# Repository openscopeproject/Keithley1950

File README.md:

# Keithley 195A DMM Option 1950

Keithley Instruments 195A Digital Multimeter is a 5½ digit resolution 200 000
count instrument that was manufactured in the 80's, possibly early 90's. It was
available in two configurations: base model that only had DC Volts and Ohms
measurements and model with 1950 option, which added DC/AC Amps and AC TRMS
Volts measurements.

Keithley DMM line has long replaced 195/196/199 series with newer models but
these still show up on Ebay and other outlets and they offer great performance
for reasonable prices. Unfortunately most of the 195A models available online
are the ones without 1950 Option.

This project aims to recreate the 1950 Option PCB and circuitry using modern
components.

In the process some upgrades and some compromises were made. For example this
version of 1950 option board is based on AD8436 trms chip that along with newer
opamps provides higher bandwidth and better overall specs than much older AD536
of the original. On the other hand cheaper shunt resistors are used (because
of their availability) with worse drift and tempco characteristics.

**High voltage** operation using the new board is also **NOT** recommended or
tested.

---

## BOM

See [bom](https://openscopeproject.org/InteractiveHtmlBomDemo/html/Keithley1950.html)
for this board generated by
[InteractiveHtmlBom](https://github.com/openscopeproject/InteractiveHtmlBom)
plugin for KiCad.

## Schematic

## 3D render

## Pictures

End result installed in the meter

Original board next to new version

Close up of rev A board with Genuine Bodge™ visible on the left

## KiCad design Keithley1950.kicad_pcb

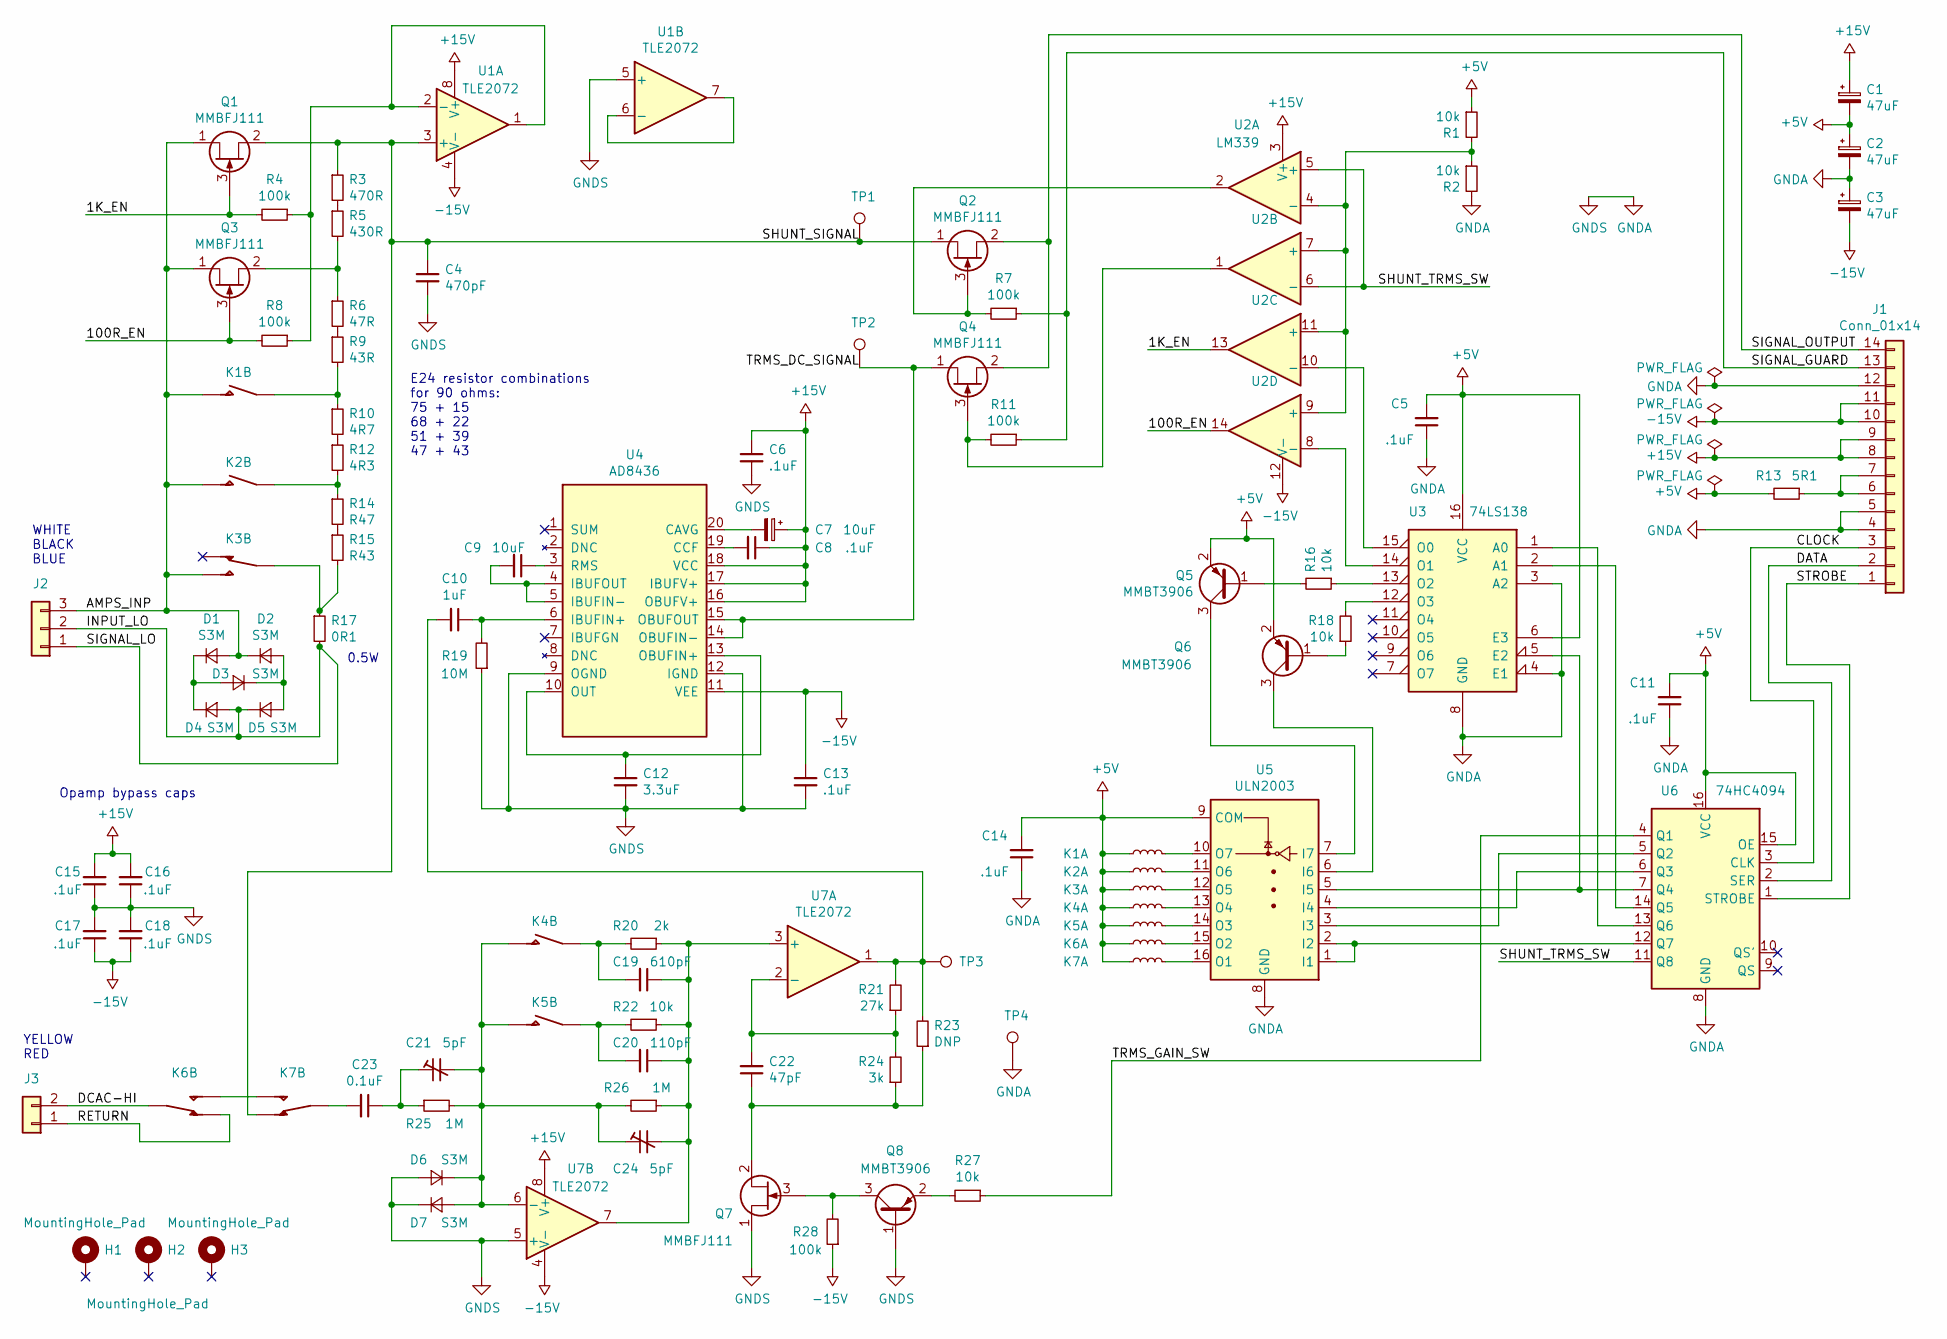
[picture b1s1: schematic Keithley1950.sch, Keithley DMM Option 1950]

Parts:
C1, C2, C3: 47uF; CP_Elec_6.3x5.9
C4: 470pF; C_0805_2012Metric
C5, C6, C8, C11, C13, C14, C15, C16, C17, C18: .1uF; C_0603_1608Metric
C7: 10uF; CP_EIA-3528-21_Kemet-B
C9: 10uF; C_0805_2012Metric
C10: 1uF; C_0805_2012Metric
C12: 3.3uF; C_0805_2012Metric
C19: 610pF; C_0805_2012Metric
C20: 110pF; C_0805_2012Metric
C21, C24: 5pF; MURATA_TZ03
C22: 47pF; C_0805_2012Metric
C23: 0.1uF; C_Rect_L18.0mm_W5.0mm_P15.00mm_FKS3_FKP3
D1, D2, D3, D4, D5, D6, D7: S3M; D_SMB
H1, H2, H3: MountingHole_Pad; MountingHole_3.2mm_M3_Pad_Via
J1: Conn_01x14; DIP-14_W7.62mm_Socket_LongPads
J2: Conn_01x03; TerminalBlock_Phoenix_PT-1,5-3-5.0-H_1x03_P5.00mm_Horizontal
J3: Conn_01x02; TerminalBlock_Phoenix_PT-1,5-2-5.0-H_1x02_P5.00mm_Horizontal
K1, K2, K4, K5: Relay_SP2P; Relay_SPST_StandexMeder_SIL_Form1A
K3, K6, K7: Relay_SP3P; Relay_SPDT_SANYOU_SRD_Series_Form_C
Q1, Q2, Q3, Q4, Q7: MMBFJ111; SOT-23
Q5, Q6, Q8: MMBT3906; SOT-23
R1, R2, R16, R18, R22, R27: 10k; R_0805_2012Metric
R3: 470R; R_0805_2012Metric
R4, R7, R8, R11, R28: 100k; R_0805_2012Metric
R5: 430R; R_0805_2012Metric
R6: 47R; R_0805_2012Metric
R9: 43R; R_0805_2012Metric
R10: 4R7; R_0805_2012Metric
R12: 4R3; R_0805_2012Metric
R13: 5R1; R_2512_6332Metric
R14: R47; R_2512_6332Metric
R15: R43; R_2512_6332Metric
R17: 0R1; R_2512_With_10mm_axial
R19: 10M; R_0805_2012Metric
R20: 2k; R_0805_2012Metric
R21: 27k; R_0805_2012Metric
R23: DNP; R_0805_2012Metric
R24: 3k; R_0805_2012Metric
R25, R26: 1M; R_0805_2012Metric
TP1, TP2, TP3: TestPoint; TestPoint_Pad_D2.5mm
TP4: TestPoint; TestPoint_THTPad_D1.5mm_Drill0.7mm
U1, U7: TLE2072; SOIC-8_3.9x4.9mm_P1.27mm
U2: LM339; SOIC-14_3.9x8.7mm_P1.27mm
U3: 74LS138; SOIC-16_3.9x9.9mm_P1.27mm
U4: AD8436; QSOP-20_3.9x8.7mm_P0.635mm
U5: ULN2003; SOIC-16_3.9x9.9mm_P1.27mm
U6: 74HC4094; SOIC-16_3.9x9.9mm_P1.27mm

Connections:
+5V: C1.2, C2.1, C5.2, C11.2, C14.2, K1.3, K2.3, K3.2, K4.3, K5.3, K6.2, K7.2, Q5.2 (E), Q6.2 (E), R1.1, R13.2, U3.6 (E3), U3.16 (VCC), U5.9 (COM), U6.15 (OE), U6.16 (VCC)
+15V: C1.1, C6.1, C7.1, C8.1, C15.2, C16.2, J1.8, J1.9, U1.8 (V+), U2.3 (V+), U4.16 (OBUFV+), U4.17 (IBUFV+), U4.18 (VCC), U7.8 (V+)
-15V: C3.2, C13.1, C17.1, C18.1, J1.10, J1.11, R28.1, U1.4 (V-), U2.12 (V-), U4.11 (VEE), U7.4 (V-)
/1K_EN: Q1.3 (G), R4.2, U2.13
/100R_EN: Q3.3 (G), R8.2, U2.14
/AMPS_INP: D1.2 (A), D2.1 (K), J2.3, K1.7, K2.7, K3.3, Q1.1 (D), Q3.1 (D)
/CLOCK: J1.3, U6.3 (CLK)
/DATA: J1.2, U6.2 (SER)
/DCAC-HI: J3.2, K6.1
/INPUT_LO: D4.2 (A), D5.1 (K), J2.1, J2.2, R17.2
/RETURN: J3.1, K6.4
/SHUNT_SIGNAL: C4.1, K7.4, Q1.2 (S), Q2.1 (D), R3.1, TP1.1, U1.3 (+)
/SHUNT_TRMS_SW: U2.5 (+), U2.6 (-), U6.11 (Q8)
/SIGNAL_GUARD: J1.13, R7.1, R11.1
/SIGNAL_OUTPUT: J1.14, Q2.2 (S), Q4.2 (S)
/STROBE: J1.1, U6.1 (STROBE)
/TRMS_DC_SIGNAL: Q4.1 (D), TP2.1, U4.14 (OBUFIN-), U4.15 (OBUFOUT)
/TRMS_GAIN_SW: R27.1, U6.4 (Q1)
GNDA: C2.2, C3.1, C4.2, C5.1, C6.2, C11.1, C12.2, C13.2, C14.1, C15.1, C16.1, C17.2, C18.2, D6.2 (A), D7.1 (K), J1.4, J1.5, J1.12, Q7.1 (D), Q8.1 (B), R2.2, R19.1, TP4.1, U1.5 (+), U3.3 (A2), U3.4 (E1), U3.8 (GND), U4.9 (OGND), U4.12 (IGND), U5.8 (GND), U6.8 (GND), U7.5 (+)
unnamed: C7.2, U4.20 (CAVG)
unnamed: C8.2, U4.19 (CCF)
unnamed: C9.1, U4.3 (RMS)
unnamed: C9.2, U4.4 (IBUFOUT), U4.5 (IBUFIN-)
unnamed: C10.1, R19.2, U4.6 (IBUFIN+)
unnamed: C10.2, R21.2, R23.2, TP3.1, U7.1
unnamed: C12.1, U4.10 (OUT), U4.13 (OBUFIN+)
unnamed: C19.1, C20.1, C24.2, R20.1, R22.1, R26.1, U7.3 (+), U7.7
unnamed: C19.2, K4.1, R20.2
unnamed: C20.2, K5.1, R22.2
unnamed: C21.1, C23.1, R25.1
unnamed: C21.2, C24.1, D6.1 (K), D7.2 (A), K4.7, K5.7, R25.2, R26.2, U7.6 (-)
unnamed: C22.1, Q7.2 (S), R23.1, R24.1
unnamed: C22.2, R21.1, R24.2, U7.2 (-)
unnamed: C23.2, K7.1
unnamed: D1.1 (K), D3.2 (A), D4.1 (K)
unnamed: D2.2 (A), D3.1 (K), D5.2 (A)
unnamed: J1.6, J1.7, R13.1
unnamed: K1.1, R9.2, R10.1
unnamed: K1.5, U5.10 (O7)
unnamed: K2.1, R12.2, R14.1
unnamed: K2.5, U5.11 (O6)
unnamed: K3.1, R15.2, R17.1
unnamed: K3.5, U5.12 (O5)
unnamed: K4.5, U5.13 (O4)
unnamed: K5.5, U5.14 (O3)
unnamed: K6.3, K7.3
unnamed: K6.5, U5.15 (O2)
unnamed: K7.5, U5.16 (O1)
unnamed: Q2.3 (G), R7.2, U2.2
unnamed: Q3.2 (S), R5.2, R6.1
unnamed: Q4.3 (G), R11.2, U2.1
unnamed: Q5.1 (B), R16.2
unnamed: Q5.3 (C), U5.7 (I7)
unnamed: Q6.1 (B), R18.1
unnamed: Q6.3 (C), U5.6 (I6)
unnamed: Q7.3 (G), Q8.3 (C), R28.2
unnamed: Q8.2 (E), R27.2
unnamed: R1.2, R2.1, U2.4 (-), U2.7 (+), U2.9 (+), U2.11 (+)
unnamed: R3.2, R5.1
unnamed: R4.1, R8.1, U1.1, U1.2 (-)
unnamed: R6.2, R9.1
unnamed: R10.2, R12.1
unnamed: R14.2, R15.1
unnamed: R16.1, U3.13 (O2)
unnamed: R18.2, U3.12 (O3)
unnamed: U1.6 (-), U1.7
unnamed: U2.8 (-), U3.14 (O1)
unnamed: U2.10 (-), U3.15 (O0)
unnamed: U3.1 (A0), U6.13 (Q6)
unnamed: U3.2 (A1), U6.14 (Q5)
unnamed: U3.5 (E2), U5.5 (I5), U6.7 (Q4)
unnamed: U5.1 (I1), U5.2 (I2), U6.12 (Q7)
unnamed: U5.3 (I3), U6.5 (Q2)
unnamed: U5.4 (I4), U6.6 (Q3)

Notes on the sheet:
WHITE BLACK BLUE
YELLOW RED
E24 resistor combinations for 90 ohms: 75 + 15 68 + 22 51 + 39 47 + 43
Opamp bypass caps
0.5W

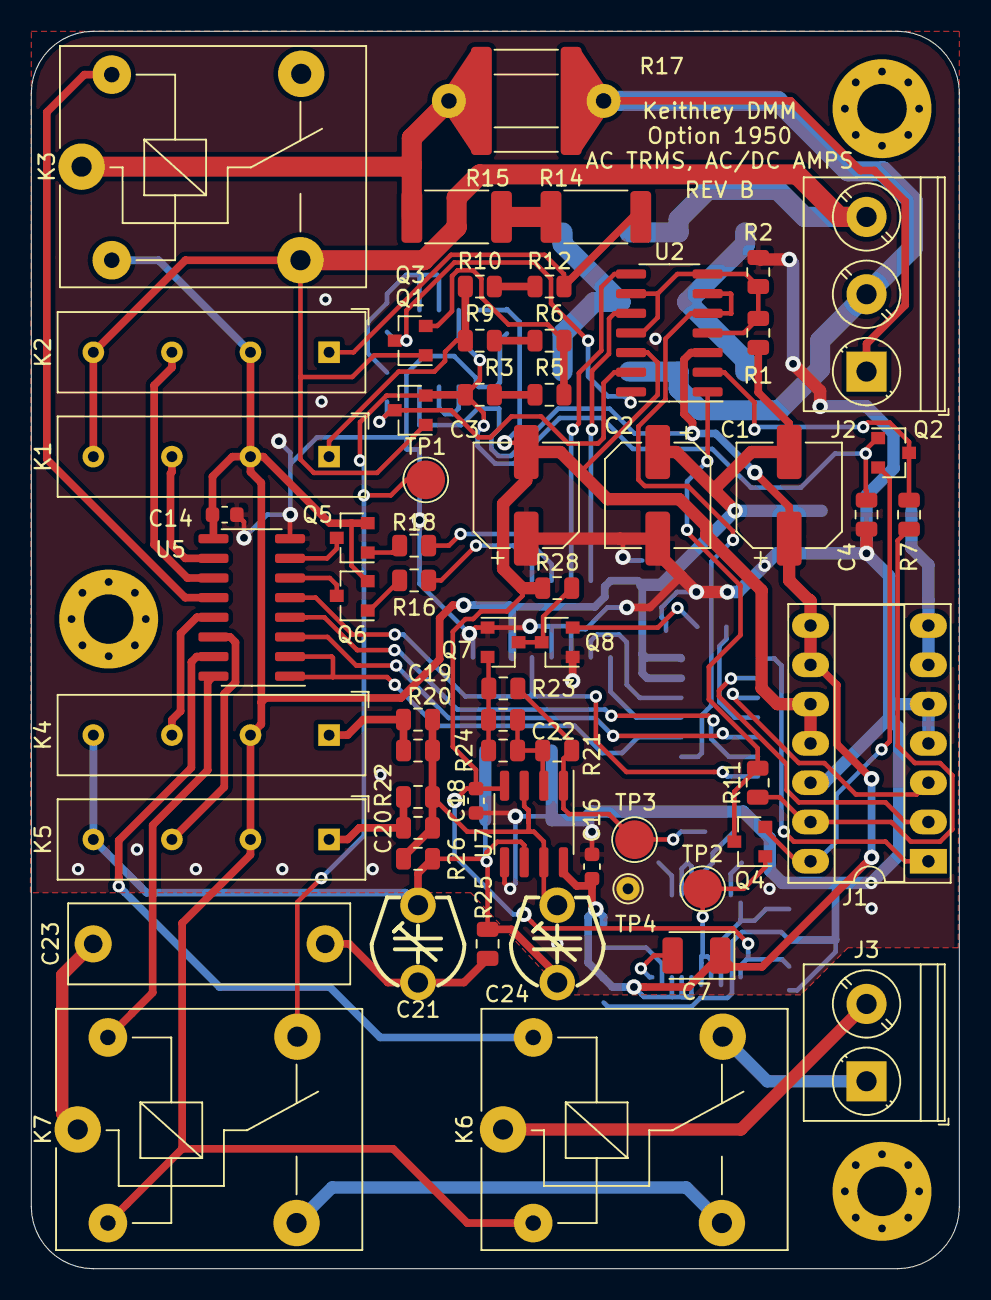
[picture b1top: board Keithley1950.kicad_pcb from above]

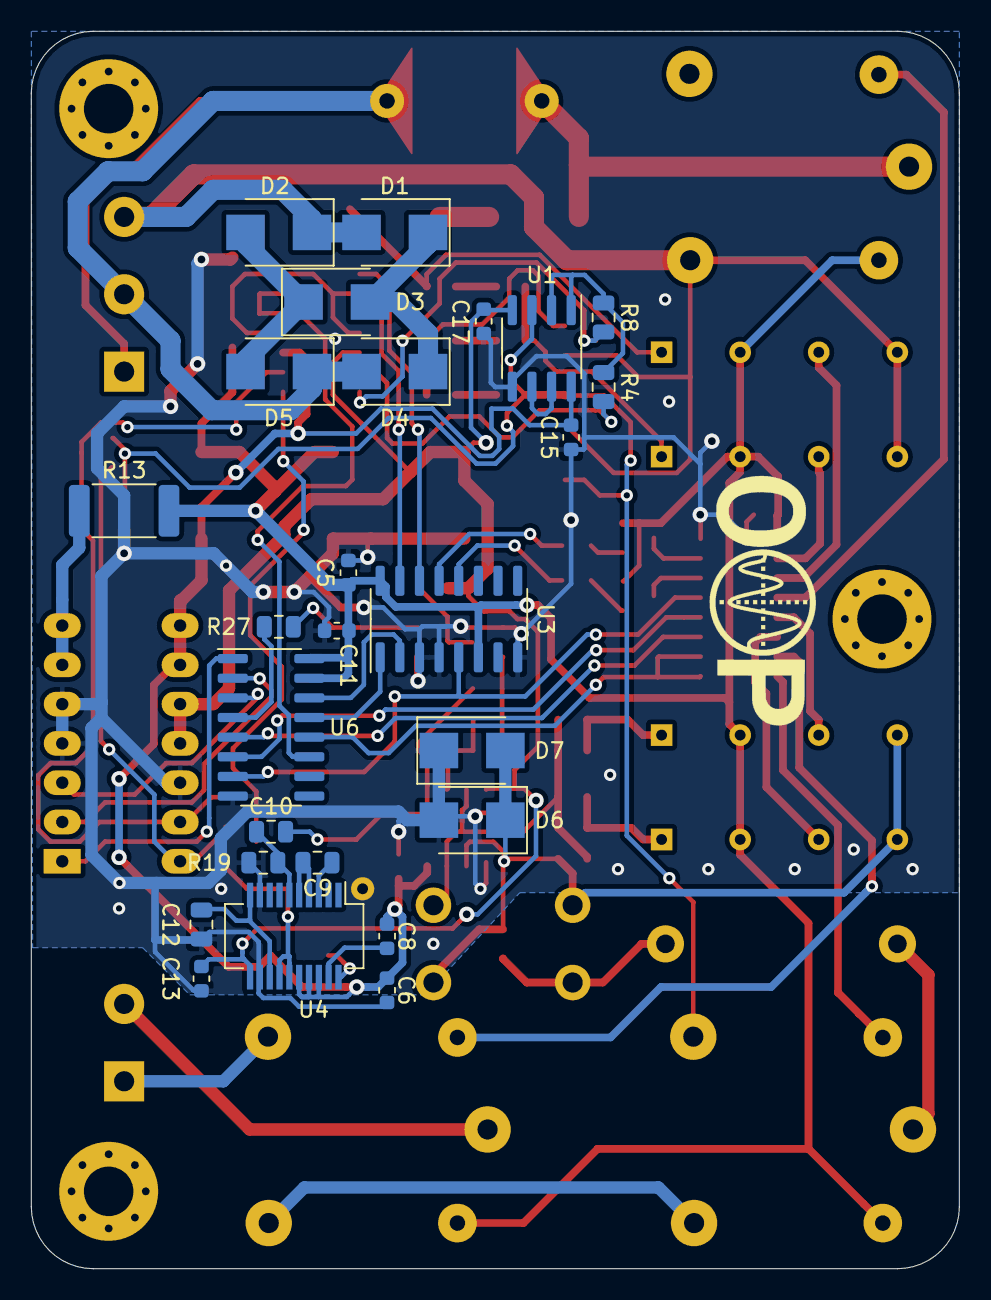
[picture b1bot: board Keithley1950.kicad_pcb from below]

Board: 2 copper layers, 60.0 x 80.0 mm, 92 parts (27 on the bottom side), 74 nets.

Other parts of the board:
LOGO***: LOGO; osp-logo

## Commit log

2019-04-15 First schematic pass
2019-05-03 Schematic work
2019-05-06 More schematic work, put some values in
2019-05-30 Almost all components fully specified
2019-05-30 Switched to AD8436, finished schematic
2019-06-01 Switch to 2 serial resistors for shunts in schematic
2019-06-01 Add TZ03 model, some tweaks
2019-06-03 Add constantan spiral model
2019-06-19 Initial placement on pcb
2019-06-23 Optimized placement
2019-06-23 More optimizations
2019-06-24 Manual routing done
2019-06-24 Clean up silkscreen, add logos
2019-06-24 Add metadata, generate bom
2019-06-24 Fix input sense track overlap
2019-07-04 Fixes, tweaks, tag rev A
2019-11-17 Revision B
    1. Clearance for high voltage lines
    2. 14 pin connector courtyard overlap
    3. 24K resistor is DNP
    4. Fix swapped inputs of U7B
    5. Change c7 to tantalum type Bx
2020-01-19 Regenerate bom
2020-01-19 Replot gerbers
